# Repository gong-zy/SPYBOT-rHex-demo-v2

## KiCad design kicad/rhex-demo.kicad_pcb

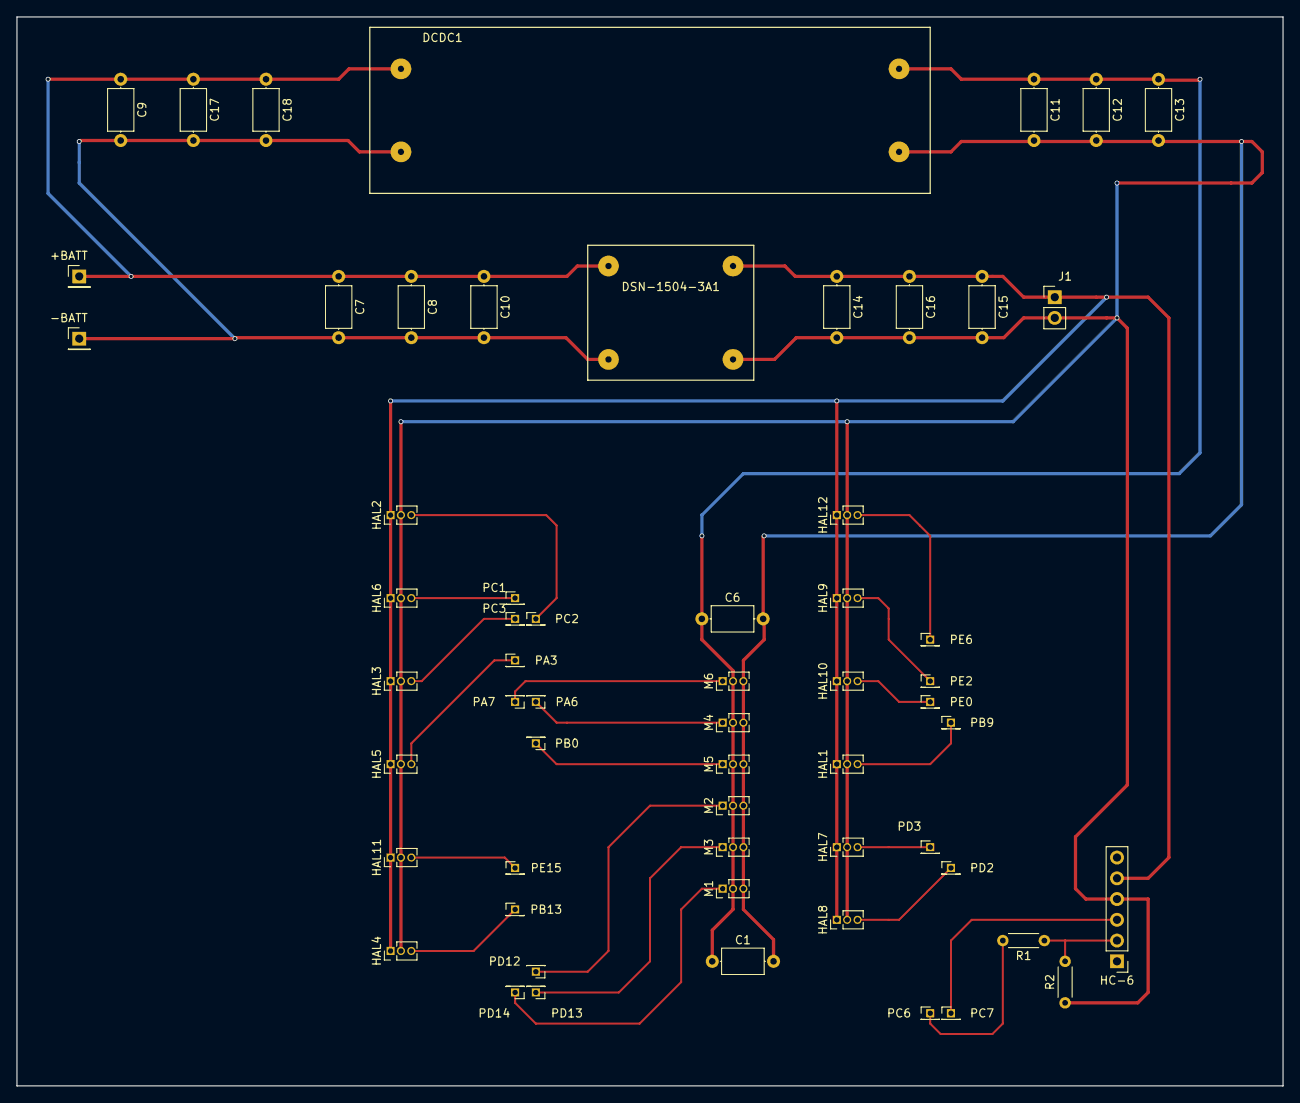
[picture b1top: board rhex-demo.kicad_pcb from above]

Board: 2 copper layers, 154.9 x 130.8 mm, 60 parts (0 on the bottom side), 6 nets.

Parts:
+BATT: Pin_Header_Straight_1x01_Pitch2.54mm
-BATT: Pin_Header_Straight_1x01_Pitch2.54mm
C1, C6: 470uF; C_Axial_L5.1mm_D3.1mm_P7.50mm_Horizontal
C7, C9, C11, C14: 10uF; C_Axial_L5.1mm_D3.1mm_P7.50mm_Horizontal
C8, C12, C15, C17: 100nF; C_Axial_L5.1mm_D3.1mm_P7.50mm_Horizontal
C10, C13, C16, C18: 100pF; C_Axial_L5.1mm_D3.1mm_P7.50mm_Horizontal
DCDC1: DCDC-6010-M
DSN-1504-3A1: DCDC2; DSN-1504-2A1
HAL1, HAL2, HAL3, HAL4, HAL5, HAL6, HAL7, HAL8, HAL9, HAL10, HAL11, HAL12: TLE4905L; Pin_Header_Straight_1x03_Pitch1.27mm
HC-6: HC-06-bluetooth; Socket_Strip_Straight_1x06_Pitch2.54mm
J1: MCU power; Pin_Header_Straight_1x02_Pitch2.54mm
M1, M2, M3, M4, M5, M6: Motor_Servo; Pin_Header_Straight_1x03_Pitch1.27mm
PA3, PA6, PA7: GPIO_PIN; Pin_Header_Straight_1x01_Pitch1.27mm
PB0, PB9, PB13: GPIO_PIN; Pin_Header_Straight_1x01_Pitch1.27mm
PC1, PC2, PC3, PC6, PC7: GPIO_PIN; Pin_Header_Straight_1x01_Pitch1.27mm
PD2, PD3, PD12, PD13, PD14: GPIO_PIN; Pin_Header_Straight_1x01_Pitch1.27mm
PE0, PE2, PE6, PE15: GPIO_PIN; Pin_Header_Straight_1x01_Pitch1.27mm
R1: 10k; R_Axial_DIN0204_L3.6mm_D1.6mm_P5.08mm_Horizontal
R2: 20k; R_Axial_DIN0204_L3.6mm_D1.6mm_P5.08mm_Horizontal

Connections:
+BATT: C7.1, C8.1, C9.1, C10.1, C17.1, C18.1, DCDC1.1
-BATT: C7.2, C8.2, C9.2, C10.2, C17.2, C18.2, DCDC1.2
GND: C1.2, C6.2, C11.2, C12.2, C13.2, C14.2, C15.2, C16.2, DCDC1.4, DSN-1504-3A1.4, HAL1.2, HAL2.2, HAL3.2, HAL4.2, HAL5.2, HAL6.2, HAL7.2, HAL8.2, HAL9.2, HAL10.2, HAL11.2, HAL12.2, J1.2, M1.3, M2.3, M3.3, M4.3, M5.3, M6.3, R2.1
unnamed: C1.1, C6.1, C11.1, C12.1, C13.1, DCDC1.3, M1.2, M2.2, M3.2, M4.2, M5.2, M6.2
unnamed: C14.1, C15.1, C16.1, HAL1.1, HAL2.1, HAL3.1, HAL4.1, HAL5.1, HAL6.1, HAL7.1, HAL8.1, HAL9.1, HAL10.1, HAL11.1, HAL12.1, J1.1
unnamed: R1.1, R2.2

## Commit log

2018-02-22 gitignore
2018-02-22 stm32cubemx base project
2018-02-26 project generated from stm32cubemx
    the base project generated from stm32cubemx, to atollic true studio
    peripherial inicialization done
2018-02-26 project settings
2018-03-07 stucture for servo motors with base constructor
2018-03-07 struct and inicialization modifications
2018-03-07 function to change a channels pwm-s fillrate
2018-08-29 have to start from scratch
2018-08-31 base project
2018-09-25 base project
    base project:
    -6 timer with 1kHz frequency
    -usart in async mode (115200 baud rate)
    -blue led on PD15
2018-09-30 pwm pulse setter function
2018-09-30 PWM generation enable and diable fuctions
    functions for starting and stopping pwm generations for all channels
2018-10-01 change TIM prescaler to 3
    TIM prescaler to 3, for 3 ms PWM periods
    (motors require 0.5ms to 2.5ms periods)
2018-10-01 correction for pwm pulse width
    correction for percentage pulse with specific to the motor
    0% -> 0.5 ms pulse
    100% -> 2.5 ms pulse
2018-10-01 motors stopping function, and rename motors from 0 (previously was 1)
2018-10-01 uart recive and main controll state machine
2018-10-01 uart function call correction
2018-10-01 controller android app installer
    An android app that can connect to the HC-06 bletooth module, and send the controll bytes via bluetooth. The app has 5 buttons for the 5 functions, and a GUI for connecting to the device.
2018-10-01 initial functions calls for the motors
    enable PWM generation
    stop all motors
2018-10-23 move to freeRTOS base project
    previous code can be found in branch named "none-rtos"
2018-11-03 base kicad project for shield
2018-11-05 added components for servo motors
2018-11-20 main thread for testing
2018-11-20 controll direction updates
2018-11-29 layout half done
2018-11-29 pcb layout done, generated gerb files, generated report files
2018-12-01 minor changes to layout design, regenerated prints, changed sclk to 100MHz
2018-12-02 updated forward and backward parameter
2018-12-05 add leg detection functions
2018-12-05 start leg sync imlementation
2018-12-06 add leg sync and command functions
2018-12-06 refactoring and added function description
2019-01-16 test hall sensor bypass for legs
